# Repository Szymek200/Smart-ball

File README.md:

# ⚽ SmartBall: IoT Sports Training System

SmartBall is a comprehensive hardware and software solution designed to enhance sports training by monitoring ball dynamics in real-time. The system focuses on tracking impact force and spin (angular velocity), providing athletes with immediate feedback on their performance.

This project was developed as part of the "Microprocessor and Embedded Systems" course at the Silesian University of Technology (Politechnika Śląska).

## 📂 Repository Structure

This repository is organized into three specialized modules. For detailed technical instructions and implementation logic, please refer to the documentation within each folder:

* **/mobile-app** – Android application (Kotlin) for real-time UDP data visualization, session history, and remote sensor configuration.
* **/firmware-esp32** – ESP-IDF C code featuring high-G impact detection, quaternion-based sensor fusion (complementary filter), and power management.
* **/hardware-3d** – 3D enclosure designs (PET-G), PCB schematics, and the Bill of Materials (BOM).

## ⚙️ System Architecture

The system utilizes a **Producer-Consumer** architecture to ensure high performance and low latency:

* **The Producer (ESP32):** Equipped with an **H3LIS331DL** (400g accelerometer) and an **L3G4200D** (2000 dps gyroscope). It processes raw motion data, compensates for gravity using quaternions, and detects strikes using a circular buffer to capture pre-impact telemetry.
* **The Consumer (Mobile App):** Connects to the ball via a Wi-Fi Access Point and receives processed statistics and live streams using a high-speed binary UDP protocol.

## 🚀 Quick Start Guide

1.  **Power On:** Ensure the Li-Pol battery is charged and the device is powered.
2.  **Connect Wi-Fi:** On your mobile device, connect to the SmartBall network:
    * **SSID:** `SmartBall_ESP32`
    * **Password:** `12345678`
3.  **Launch Application:** Open the SmartBall app to begin receiving data.
4.  **Analyze:** Use the "History" section to view detailed charts of every kick, including G-force and rotation speed.

## 🔋 Power Management

To maximize the 18-hour battery life, the system includes an automated Power Management Algorithm:
* **Deep Sleep:** The MCU enters deep sleep after a configurable period of inactivity.
* **Motion Wake-up:** The accelerometer remains active as a low-power motion detector, waking the ESP32 via a hardware interrupt (GPIO 32) when the ball is moved.

## 🛠 Tech Stack Summary

* **Microcontroller:** ESP32-WROOM-32 (Dual-core).
* **Firmware:** ESP-IDF (C), FreeRTOS, LwIP (UDP).
* **Mobile App:** Kotlin, Coroutines, MPAndroidChart.
* **Mechanical:** 3D Printed PET-G, Li-Pol 1580mAh, MP2636 Power Manager.

---
*Developed by Szymon Mamok | Silesian University of Technology 2025/2026*

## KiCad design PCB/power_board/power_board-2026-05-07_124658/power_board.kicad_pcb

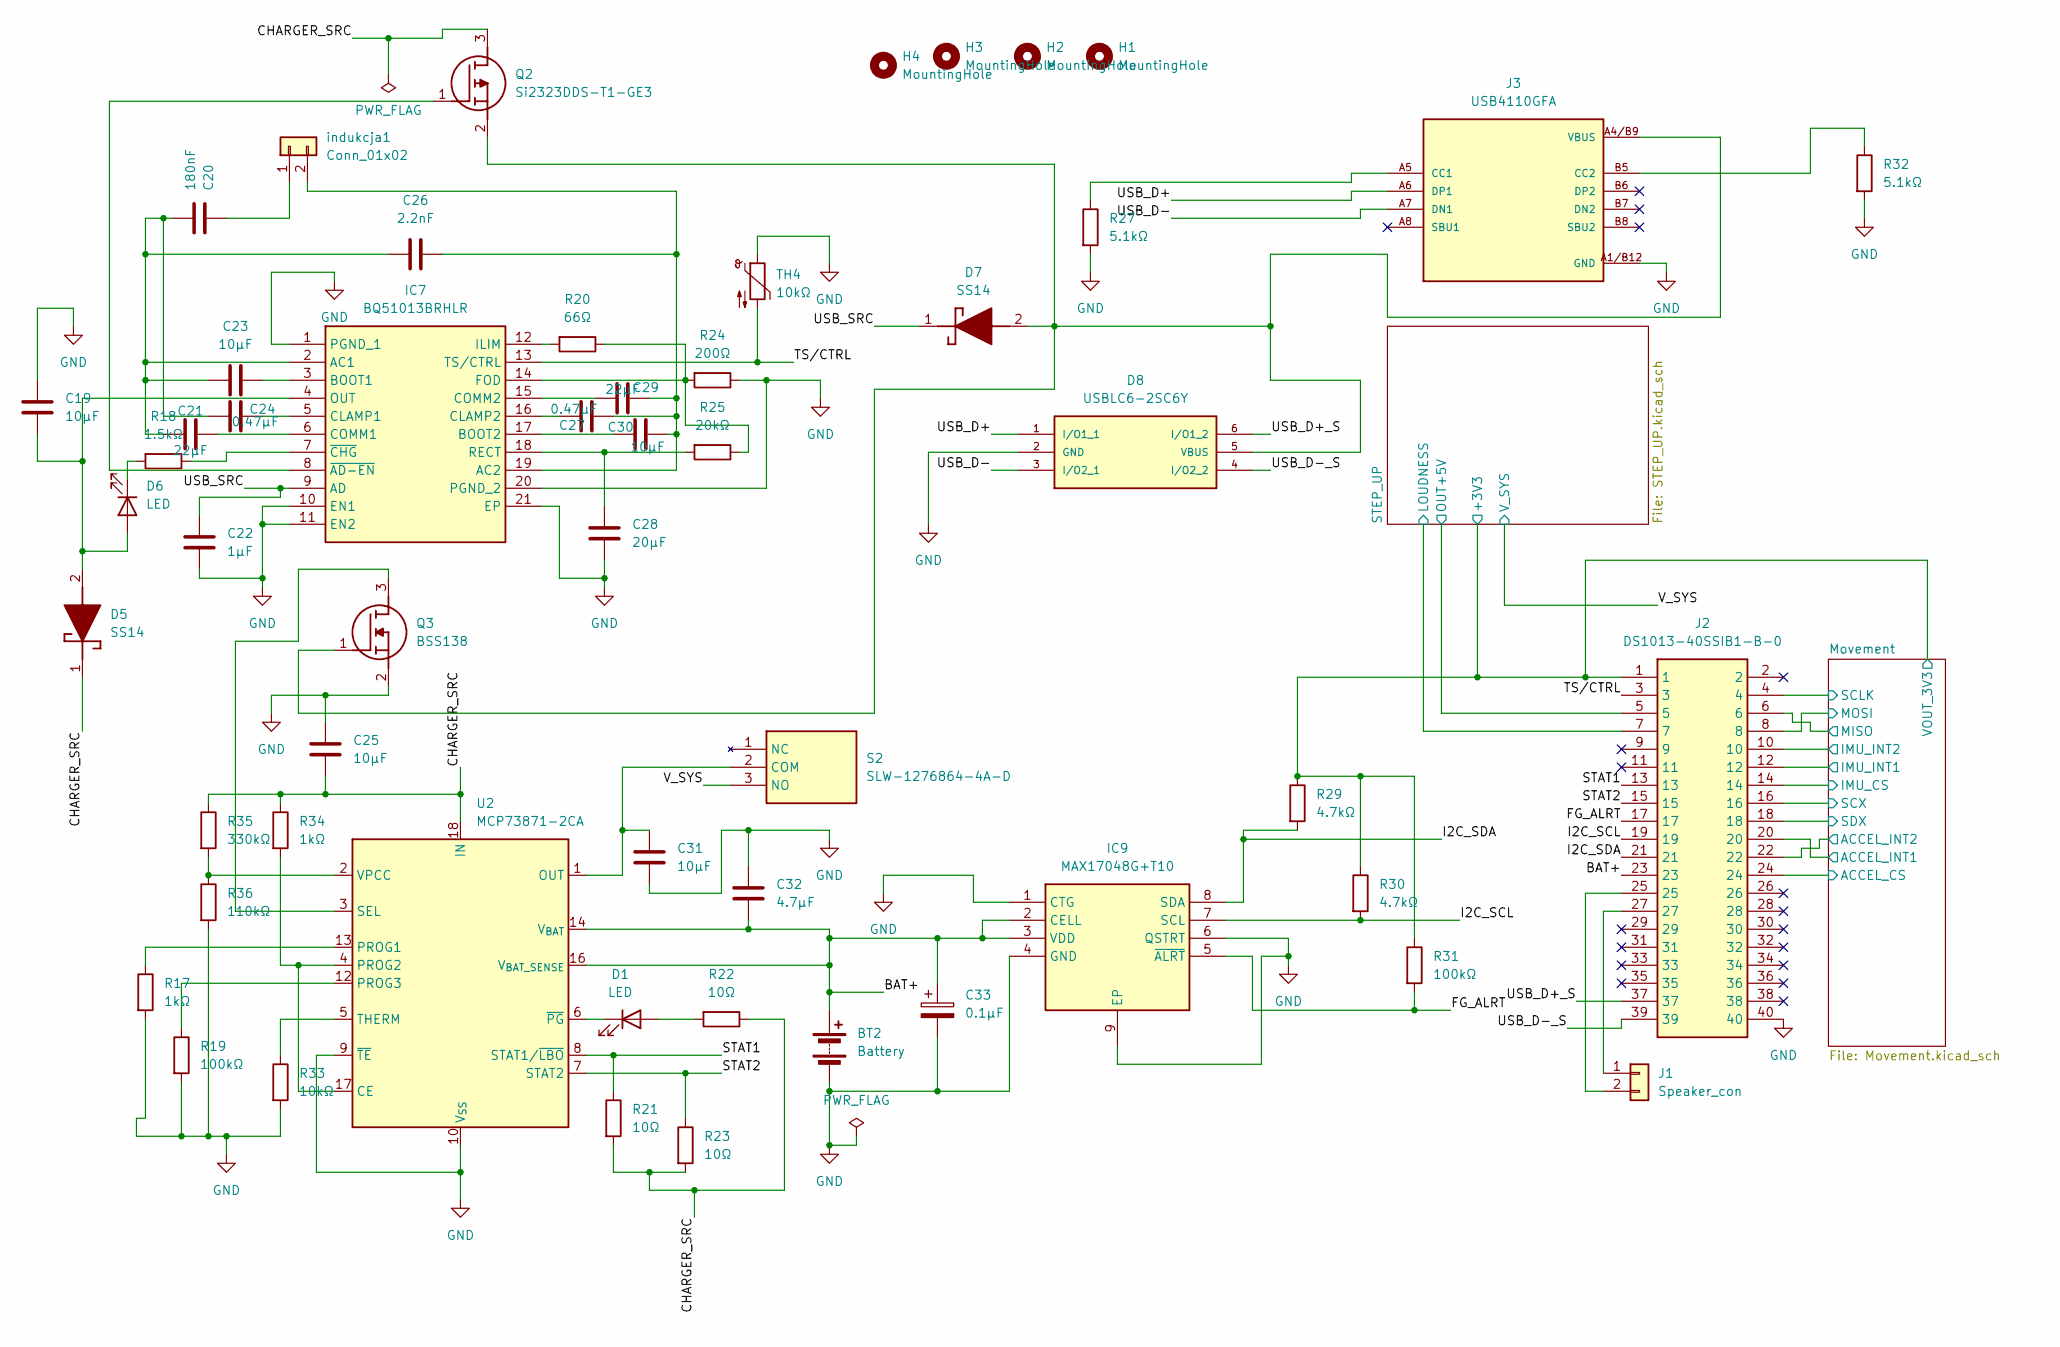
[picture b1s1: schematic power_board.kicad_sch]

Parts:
BT2: Battery; SolderWire-0.75sqmm_1x02_P4.8mm_D1.25mm_OD2.3mm
C19, C23, C25, C30, C31: 10µF; CP_EIA-3216-18_Kemet-A
C20: 180nF; CP_EIA-3216-18_Kemet-A
C21, C29: 22µF; CP_EIA-3216-18_Kemet-A
C22: 1µF; CP_EIA-3216-18_Kemet-A
C24, C27: 0.47µF; CP_EIA-3216-18_Kemet-A
C26: 2.2nF; CP_EIA-3216-18_Kemet-A
C28: 20µF; CP_EIA-3216-18_Kemet-A
C32: 4.7µF; CP_EIA-3216-18_Kemet-A
C33: 0.1µF; CP_EIA-3216-18_Kemet-A
D1, D6: LED; LED_0603_1608Metric
D5, D7: SS14; DIOM5227X270N; Mouser Part Number 512-SS14
D8: USBLC6-2SC6Y; SOT95P280X145-6N; MOUSER_PART_NUMBER 511-USBLC6-2SC6Y
H1, H2, H3, H4: MountingHole; MountingHole_3.2mm_M3_Pad_Via
IC7: BQ51013BRHLR; BQ51050BRHLR; Mouser Part Number 595-BQ51013BRHLR
IC9: MAX17048G+T10; SON50P200X200X80-9N-D; Mouser Part Number 700-MAX17048G+T10
J1: Speaker_con; PinHeader_1x02_P2.54mm_Vertical
J2: DS1013-40SSIB1-B-0; DS101340SSIB1B0; Manufacturer_Part_Number DS1013-40SSIB1-B-0
J3: USB4110GFA; GCT_USB4110GFA
Q2: Si2323DDS-T1-GE3; SOT95P237X112-3N; Mouser Part Number 78-SI2323DDS-T1-GE3
Q3: BSS138; SOT95P240X120-3N; Mouser Part Number 512-BSS138
R17, R34: 1kΩ; R_0603_1608Metric
R18: 1.5kΩ; R_0603_1608Metric
R19, R31: 100kΩ; R_0603_1608Metric
R20: 66Ω; R_0603_1608Metric
R21, R22, R23: 10Ω; R_0603_1608Metric
R24: 200Ω; R_0603_1608Metric
R25: 20kΩ; R_0603_1608Metric
R27, R32: 5.1kΩ; R_0603_1608Metric
R29, R30: 4.7kΩ; R_0603_1608Metric
R33: 10kΩ; R_0603_1608Metric
R35: 330kΩ; R_0603_1608Metric
R36: 110kΩ; R_0603_1608Metric
S2: SLW-1276864-4A-D; SLW12768644AD; Mouser Part Number 179-SLW-1276864-4A-D
TH4: 10kΩ; R_0603_1608Metric
U2: MCP73871-2CA; QFN-20-1EP_4x4mm_P0.5mm_EP2.5x2.5mm
indukcja1: Conn_01x02; PinHeader_1x02_P2.54mm_Vertical

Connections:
/BAT+: BT2.1 (+), C32.2, C33.1, IC9.2 (CELL), IC9.3 (VDD), J2.23, U2.14 (V_{BAT}), U2.15 (V_{BAT}), U2.16 (V_{BAT_SENSE})
/CHARGER_SRC: C25.2, D5.1 (K), Q2.3 (D), R21.2, R22.1, R23.2, R34.1, R35.1, U2.18 (IN), U2.19 (IN)
/FG_ALRT: IC9.5 (~ALRT), J2.17, R31.2
/I2C_SCL: IC9.7 (SCL), J2.19, R30.2
/I2C_SDA: IC9.8 (SDA), J2.21, R29.2
/Movement/ACCEL_CS: J2.24; also elsewhere on the board
/Movement/ACCEL_INT1: J2.20; also elsewhere on the board
/Movement/ACCEL_INT2: J2.22; also elsewhere on the board
/Movement/IMU_CS: J2.14; also elsewhere on the board
/Movement/IMU_INT1: J2.12; also elsewhere on the board
/Movement/IMU_INT2: J2.10; also elsewhere on the board
/Movement/MISO: J2.6; also elsewhere on the board
/Movement/MOSI: J2.8; also elsewhere on the board
/Movement/SCLK: J2.4; also elsewhere on the board
/Movement/SCX: J2.16; also elsewhere on the board
/Movement/SDX: J2.18; also elsewhere on the board
/Movement/VOUT_3V3: J2.1, R29.1, R30.1, R31.1; also elsewhere on the board
/STAT1: J2.13, R21.1, U2.8 (STAT1/~LBO)
/STAT2: J2.15, R23.1, U2.7 (STAT2)
/STEP_UP/LOUDNESS: J2.7; also elsewhere on the board
/STEP_UP/OUT+5V: J2.5; also elsewhere on the board
/TS/CTRL: IC7.13 (TS/CTRL), J2.3, TH4.2
/USB_D+: D8.1 (I/O1_1), J3.A6 (DP1)
/USB_D+_S: D8.6 (I/O1_2), J2.37
/USB_D-: D8.3 (I/O2_1), J3.A7 (DN1)
/USB_D-_S: D8.4 (I/O2_2), J2.39
/USB_SRC: C22.1, D7.1 (K), IC7.9 (AD)
/V_SYS: S2.3 (NO); also elsewhere on the board
GND: BT2.2 (-), C19.2, C22.2, C25.1, C28.2, C31.2, C32.1, C33.2, D8.2 (GND), IC7.1 (PGND_1), IC7.10 (EN1), IC7.11 (EN2), IC7.20 (PGND_2), IC7.21 (EP), IC9.1 (CTG), IC9.4 (GND), IC9.6 (QSTRT), IC9.9 (EP), J2.40, J3.A1/B12 (GND), J3.B1/A12 (GND), J3.S1 (GND), J3.S2 (GND), J3.S3 (GND), J3.S4 (GND), Q3.2 (S), R17.2, R19.2, R24.1, R27.2, R32.2, R33.2, R36.2, TH4.1, U2.9 (~TE), U2.10 (V_{SS}), U2.11 (V_{SS}), U2.21 (V_{SS}); also elsewhere on the board
unnamed: D1.2 (A), R22.2
unnamed: D1.1 (K), U2.6 (~PG)
unnamed: C19.1, D5.2 (A), D6.2 (A), IC7.4 (OUT)
unnamed: D6.1 (K), R18.2
unnamed: C20.2, C21.2, C23.2, C24.2, C26.2, IC7.2 (AC1)
unnamed: C26.1, C27.1, C29.1, C30.1, IC7.19 (AC2), indukcja1.2
unnamed: C23.1, IC7.3 (BOOT1)
unnamed: C30.2, IC7.17 (BOOT2)
unnamed: C24.1, IC7.5 (CLAMP1)
unnamed: C27.2, IC7.16 (CLAMP2)
unnamed: C21.1, IC7.6 (COMM1)
unnamed: C29.2, IC7.15 (COMM2)
unnamed: IC7.14 (FOD), R20.1, R24.2, R25.1
unnamed: IC7.12 (ILIM), R20.2
unnamed: C28.1, IC7.18 (RECT), R25.2
unnamed: IC7.8 (~AD-EN), Q2.1 (G)
unnamed: IC7.7 (~CHG), R18.1
unnamed: J1.1, J2.27
unnamed: J1.2, J2.25
unnamed: J3.A5 (CC1), R27.1
unnamed: J3.B5 (CC2), R32.1
unnamed: Q3.3 (D), U2.3 (SEL)
unnamed: C31.1, S2.2 (COM), U2.1 (OUT), U2.20 (OUT)
unnamed: R34.2, U2.4 (PROG2), U2.17 (CE)
unnamed: R17.1, U2.13 (PROG1)
unnamed: R19.1, U2.12 (PROG3)
unnamed: R33.1, U2.5 (THERM)
unnamed: R35.2, R36.1, U2.2 (VPCC)
unnamed: C20.1, indukcja1.1
VBUS: D7.2 (A), D8.5 (VBUS), J3.A4/B9 (VBUS), J3.B4/A9 (VBUS), Q2.2 (S), Q3.1 (G)

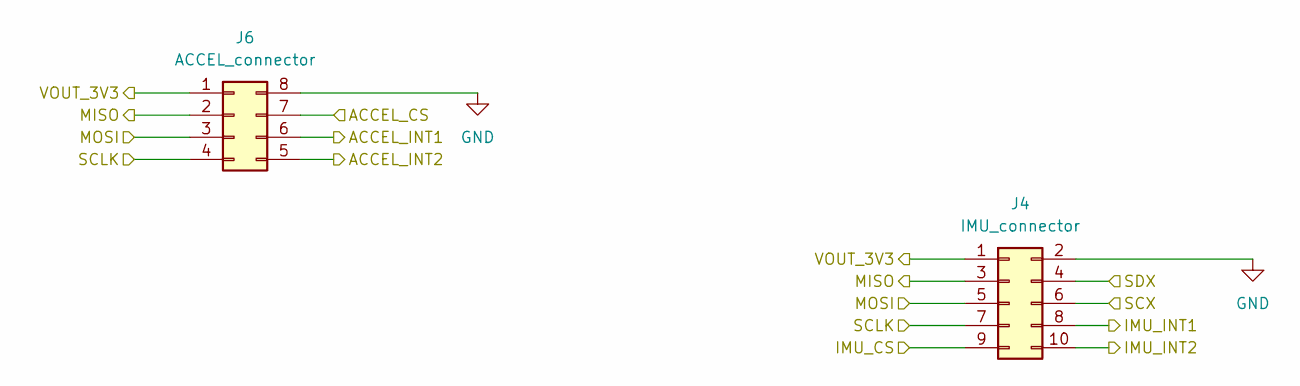
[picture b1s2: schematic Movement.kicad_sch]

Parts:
J4: IMU_connector; PinHeader_2x05_P2.54mm_Vertical
J6: ACCEL_connector; PinHeader_2x04_P2.54mm_Vertical

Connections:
/Movement/ACCEL_CS: J6.7; also elsewhere on the board
/Movement/ACCEL_INT1: J6.6; also elsewhere on the board
/Movement/ACCEL_INT2: J6.5; also elsewhere on the board
/Movement/IMU_CS: J4.9; also elsewhere on the board
/Movement/IMU_INT1: J4.8; also elsewhere on the board
/Movement/IMU_INT2: J4.10; also elsewhere on the board
/Movement/MISO: J4.3, J6.2; also elsewhere on the board
/Movement/MOSI: J4.5, J6.3; also elsewhere on the board
/Movement/SCLK: J4.7, J6.4; also elsewhere on the board
/Movement/SCX: J4.6; also elsewhere on the board
/Movement/SDX: J4.4; also elsewhere on the board
/Movement/VOUT_3V3: J4.1, J6.1; also elsewhere on the board
GND: J4.2, J6.8; also elsewhere on the board

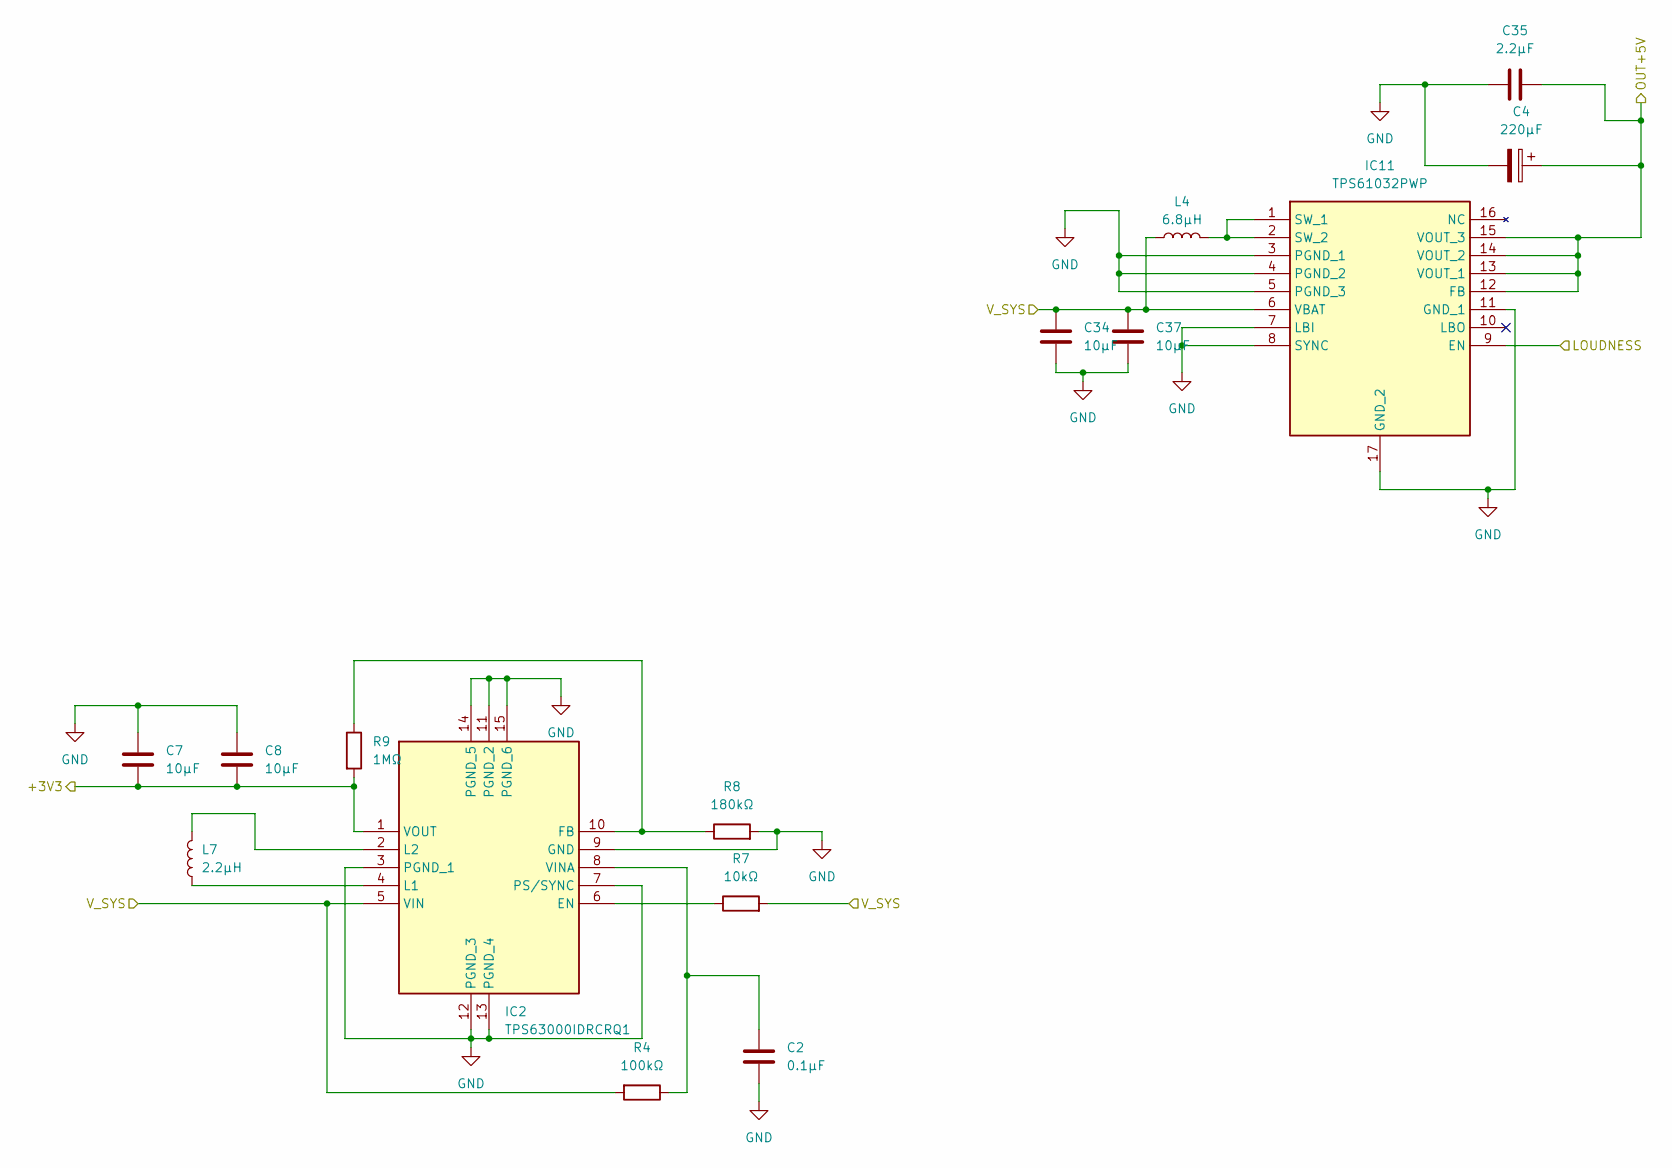
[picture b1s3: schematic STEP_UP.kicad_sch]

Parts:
C2: 0.1μF; CP_Elec_6.3x5.4
C4: 220µF; CP_Elec_6.3x5.4
C7, C8: 10μF; CP_Elec_6.3x5.4
C34, C37: 10µF; CP_Elec_6.3x5.4
C35: 2.2µF; CP_Elec_6.3x5.4
IC2: TPS63000IDRCRQ1; Mouser Part Number 595-TPS63000IDRCRQ1
IC11: TPS61032PWP; SOP65P640X120-17N; Mouser Part Number 595-TPS61032PWP
L4: 6.8µH; L_6.3x6.3_H3
L7: 2.2µH; L_6.3x6.3_H3
R4: 100kΩ; R_0603_1608Metric
R7: 10kΩ; R_0603_1608Metric
R8: 180kΩ; R_0603_1608Metric
R9: 1MΩ; R_0603_1608Metric

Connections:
/Movement/VOUT_3V3: C7.2, C8.2, IC2.1 (VOUT), R9.2; also elsewhere on the board
/STEP_UP/LOUDNESS: IC11.9 (EN); also elsewhere on the board
/STEP_UP/OUT+5V: C4.1, C35.2, IC11.12 (FB), IC11.13 (VOUT_1), IC11.14 (VOUT_2), IC11.15 (VOUT_3); also elsewhere on the board
/V_SYS: C34.1, C37.1, IC2.5 (VIN), IC11.6 (VBAT), L4.1, R4.2, R7.2; also elsewhere on the board
GND: C2.2, C4.2, C7.1, C8.1, C34.2, C35.1, C37.2, IC2.3 (PGND_1), IC2.7 (PS/SYNC), IC2.9 (GND), IC2.11 (PGND_2), IC2.12 (PGND_3), IC2.13 (PGND_4), IC2.14 (PGND_5), IC2.15 (PGND_6), IC11.3 (PGND_1), IC11.4 (PGND_2), IC11.5 (PGND_3), IC11.7 (LBI), IC11.8 (SYNC), IC11.11 (GND_1), IC11.17 (GND_2), R8.2; also elsewhere on the board
unnamed: IC2.6 (EN), R7.1
unnamed: IC2.10 (FB), R8.1, R9.1
unnamed: IC2.4 (L1), L7.1
unnamed: IC2.2 (L2), L7.2
unnamed: C2.1, IC2.8 (VINA), R4.1
unnamed: IC11.1 (SW_1), IC11.2 (SW_2), L4.2

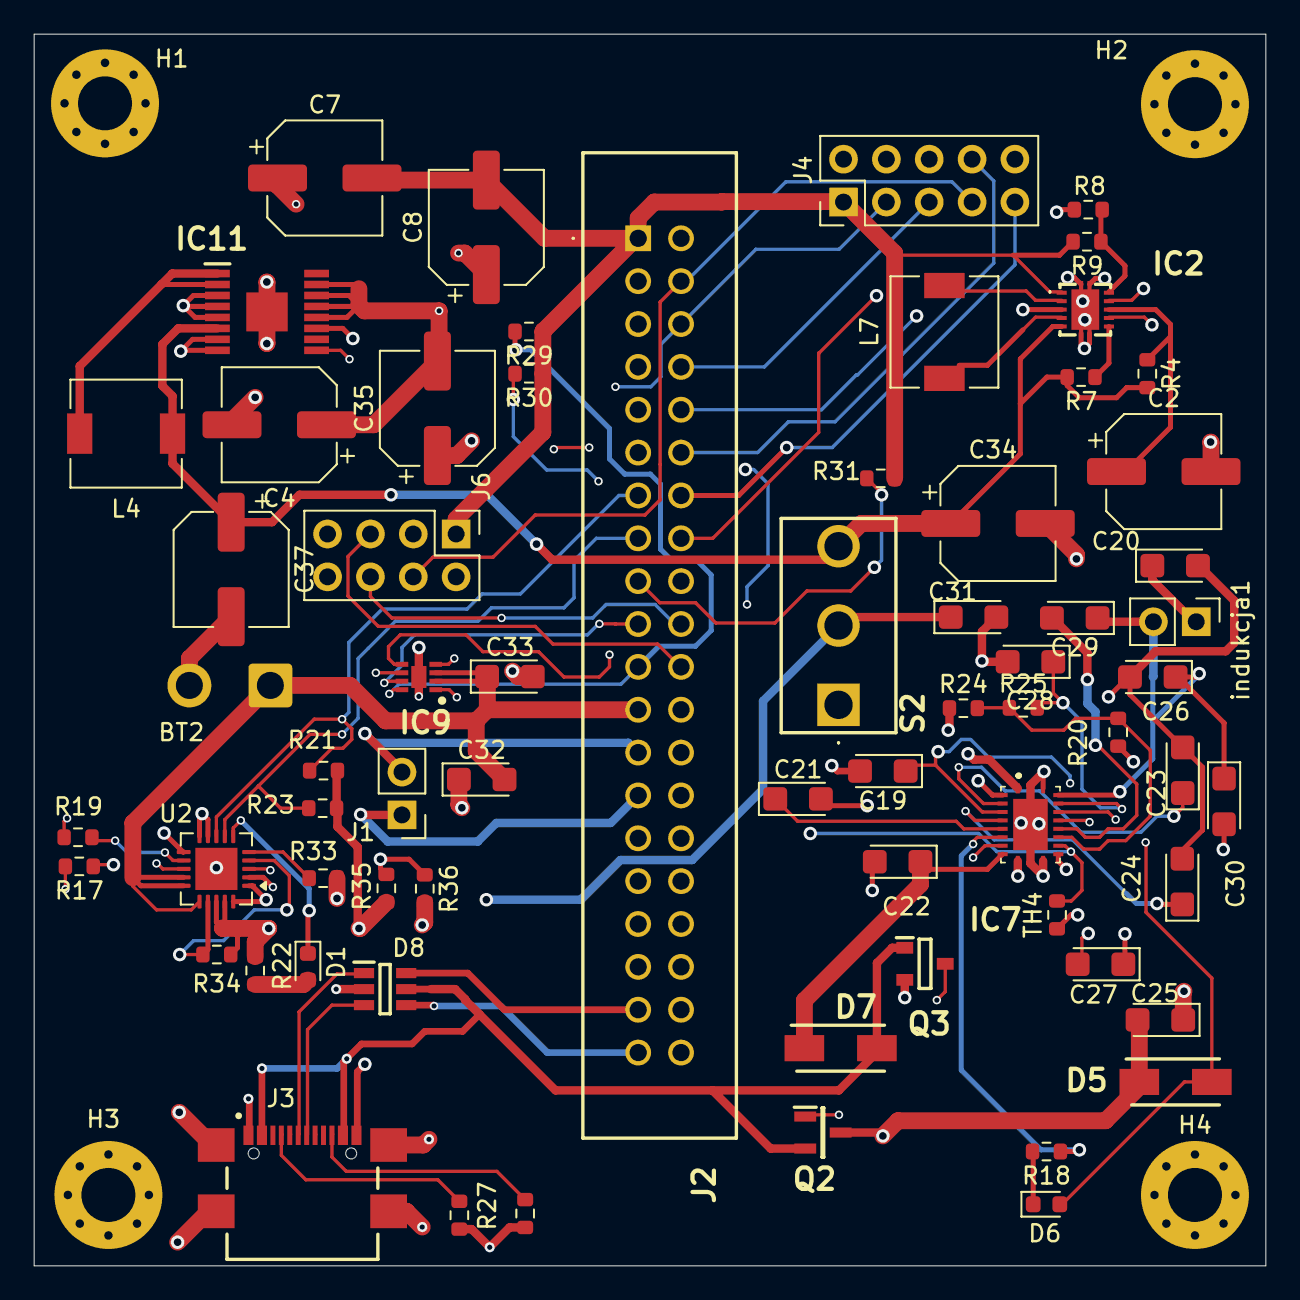
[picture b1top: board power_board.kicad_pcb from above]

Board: 4 copper layers, 73.0 x 73.0 mm, 71 parts (0 on the bottom side), 65 nets.

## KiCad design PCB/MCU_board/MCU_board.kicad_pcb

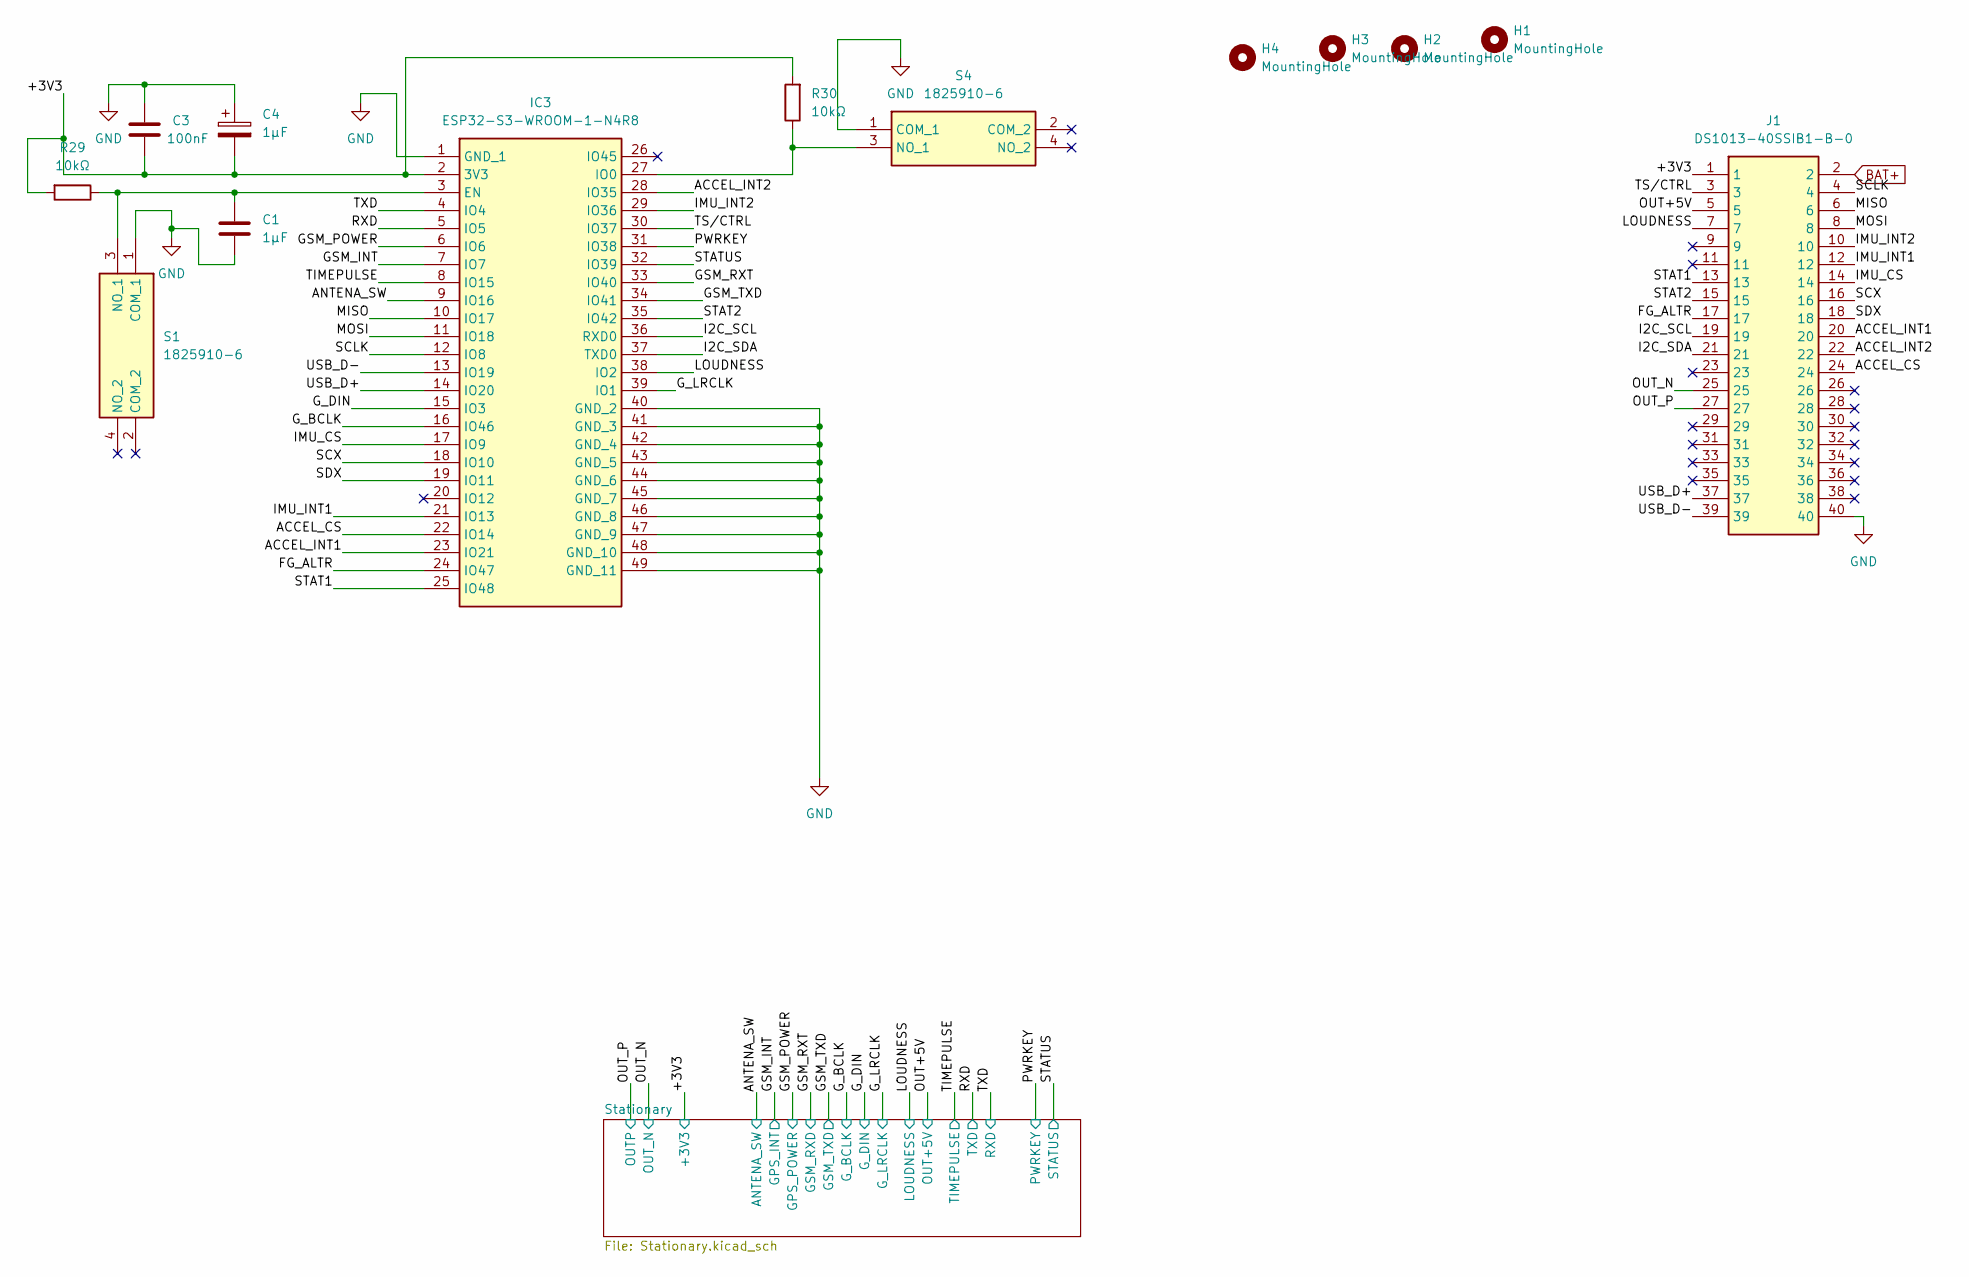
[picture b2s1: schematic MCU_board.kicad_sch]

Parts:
C1: 1μF; CP_Elec_6.3x5.4
C3: 100nF; CP_Elec_6.3x5.4
C4: 1μF; CP_EIA-3216-18_Kemet-A
H1, H2, H3, H4: MountingHole; MountingHole_3.2mm_M3_Pad_Via
IC3: ESP32-S3-WROOM-1-N4R8; ESP32S3WROOM1N4R8; Mouser Part Number 356-ESP32S3WROM1N4R8
J1: DS1013-40SSIB1-B-0; DS101340SSIB1B0; Manufacturer_Part_Number DS1013-40SSIB1-B-0
R29, R30: 10kΩ; R_0603_1608Metric
S1, S4: 1825910-6; 18259106; Manufacturer_Part_Number 1825910-6

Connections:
/+3V3: C3.2, C4.2, IC3.2 (3V3), J1.1, R29.2, R30.2; also elsewhere on the board
/ACCEL_CS: IC3.22 (IO14), J1.24
/ACCEL_INT1: IC3.23 (IO21), J1.20
/ACCEL_INT2: IC3.28 (IO35), J1.22
/ANTENA_SW: IC3.9 (IO16); also elsewhere on the board
/FG_ALTR: IC3.24 (IO47), J1.17
/GSM_INT: IC3.7 (IO7); also elsewhere on the board
/GSM_POWER: IC3.6 (IO6); also elsewhere on the board
/GSM_RXT: IC3.33 (IO40); also elsewhere on the board
/GSM_TXD: IC3.34 (IO41); also elsewhere on the board
/G_BCLK: IC3.16 (IO46); also elsewhere on the board
/G_DIN: IC3.15 (IO3); also elsewhere on the board
/G_LRCLK: IC3.39 (IO1); also elsewhere on the board
/I2C_SCL: IC3.36 (RXD0), J1.19
/I2C_SDA: IC3.37 (TXD0), J1.21
/IMU_CS: IC3.17 (IO9), J1.14
/IMU_INT1: IC3.21 (IO13), J1.12
/IMU_INT2: IC3.29 (IO36), J1.10
/LOUDNESS: IC3.38 (IO2), J1.7; also elsewhere on the board
/MISO: IC3.10 (IO17), J1.6
/MOSI: IC3.11 (IO18), J1.8
/OUT+5V: J1.5; also elsewhere on the board
/OUT_N: J1.25; also elsewhere on the board
/OUT_P: J1.27; also elsewhere on the board
/PWRKEY: IC3.31 (IO38); also elsewhere on the board
/RXD: IC3.5 (IO5); also elsewhere on the board
/SCLK: IC3.12 (IO8), J1.4
/SCX: IC3.18 (IO10), J1.16
/SDX: IC3.19 (IO11), J1.18
/STAT1: IC3.25 (IO48), J1.13
/STAT2: IC3.35 (IO42), J1.15
/STATUS: IC3.32 (IO39); also elsewhere on the board
/TIMEPULSE: IC3.8 (IO15); also elsewhere on the board
/TS/CTRL: IC3.30 (IO37), J1.3
/TXD: IC3.4 (IO4); also elsewhere on the board
/USB_D+: IC3.14 (IO20), J1.37
/USB_D-: IC3.13 (IO19), J1.39
BAT+: J1.2; also elsewhere on the board
GND: C1.2, C3.1, C4.1, IC3.1 (GND_1), IC3.40 (GND_2), IC3.41 (GND_3), IC3.42 (GND_4), IC3.43 (GND_5), IC3.44 (GND_6), IC3.45 (GND_7), IC3.46 (GND_8), IC3.47 (GND_9), IC3.48 (GND_10), IC3.49 (GND_11), J1.40, S1.1 (COM_1), S4.1 (COM_1); also elsewhere on the board
unnamed: C1.1, IC3.3 (EN), R29.1, S1.3 (NO_1)
unnamed: IC3.27 (IO0), R30.1, S4.3 (NO_1)

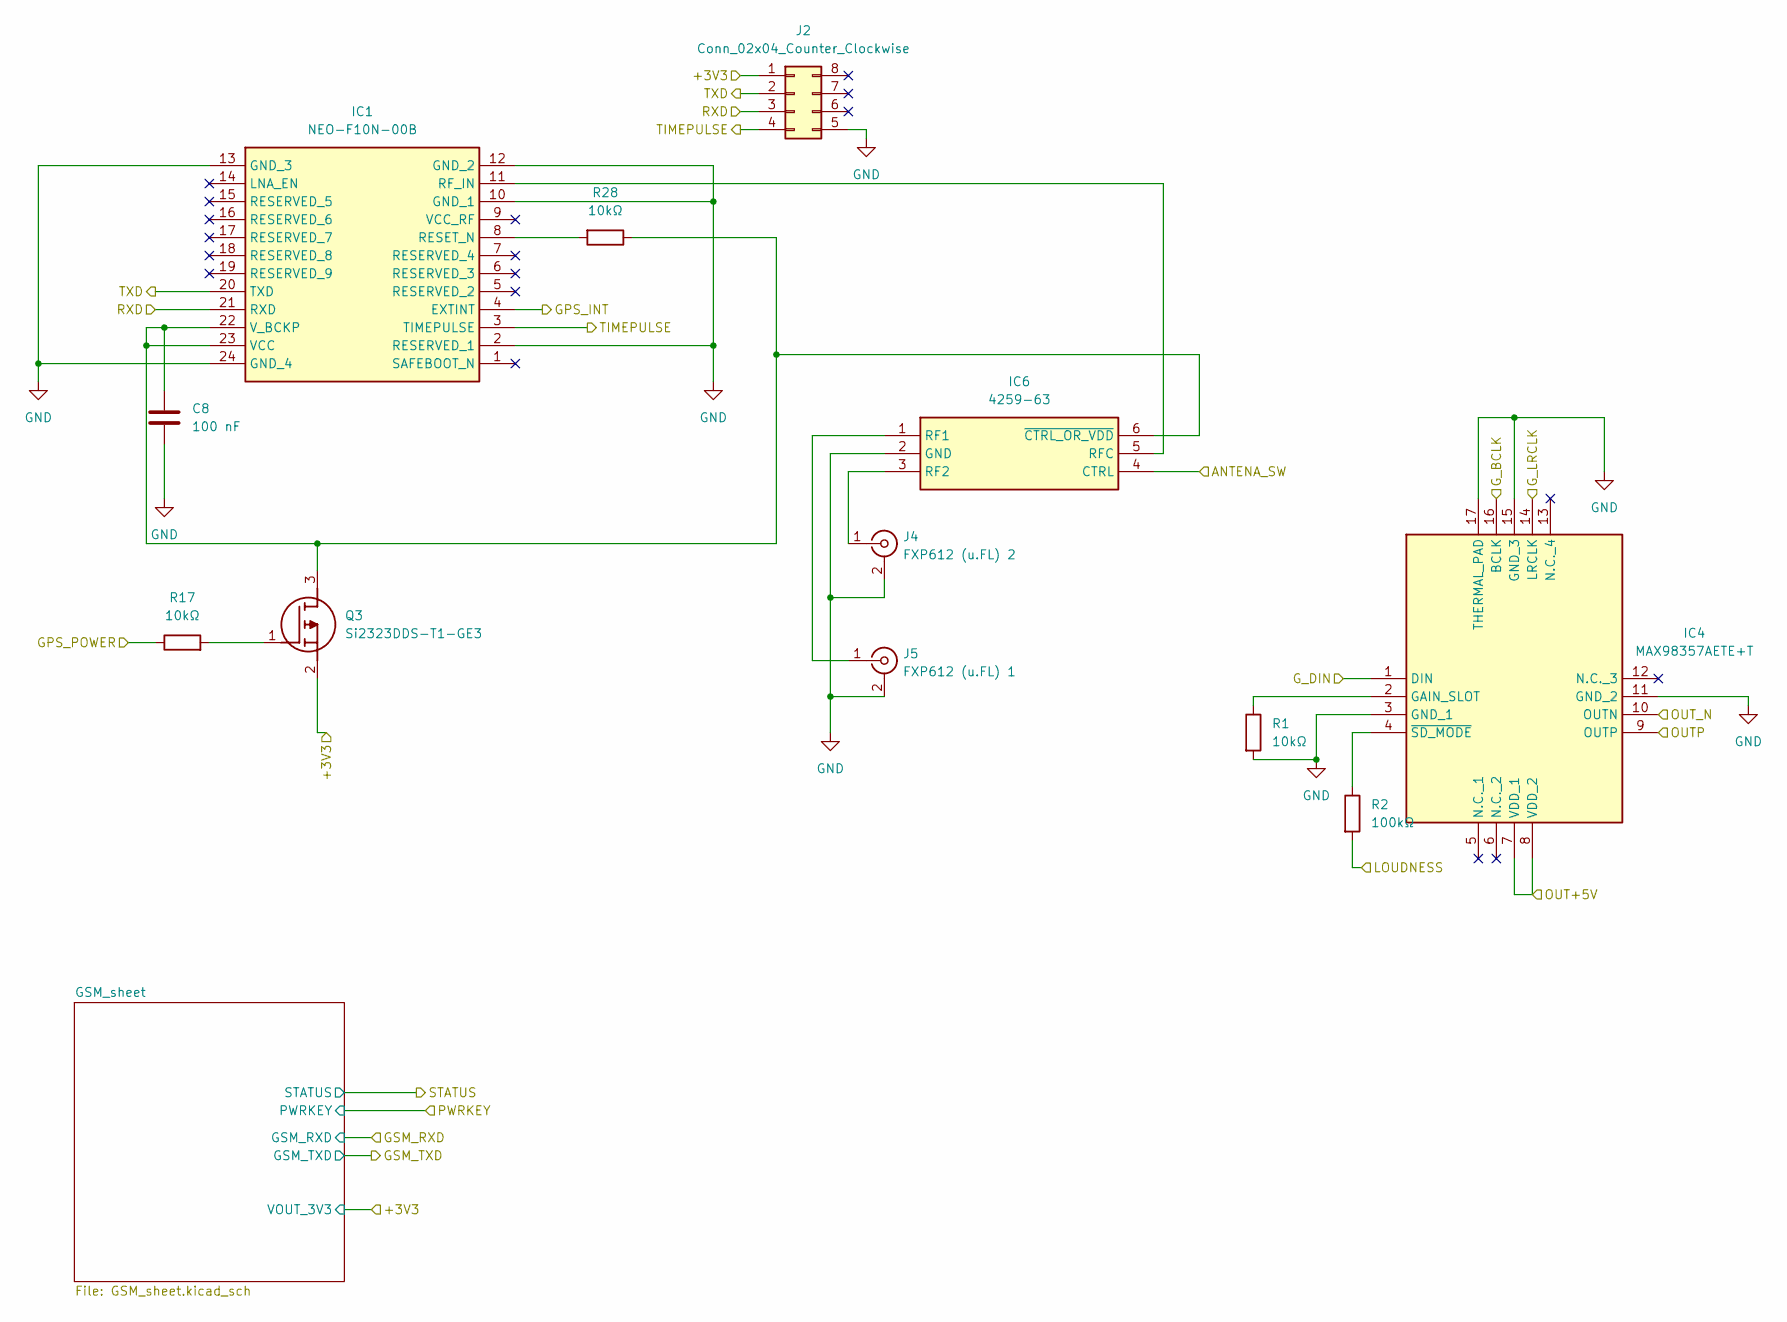
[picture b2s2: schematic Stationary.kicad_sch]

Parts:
C8: 100 nF; CP_Elec_6.3x5.4
IC1: NEO-F10N-00B; NEOF10N00B; Mouser Part Number 377-NEO-F10N-00B
IC4: MAX98357AETE+T; QFN50P300X300X80-17N; Mouser Part Number 700-MAX98357AETE+T
IC6: 4259-63; SOT65P210X110-6N; Mouser Part Number 81-4259-63
J2: Conn_02x04_Counter_Clockwise; PinHeader_2x04_P2.54mm_Vertical
J4: FXP612 (u.FL) 2; U.FL_Molex_MCRF_73412-0110_Vertical
J5: FXP612 (u.FL) 1; U.FL_Molex_MCRF_73412-0110_Vertical
Q3: Si2323DDS-T1-GE3; SOT-23; Mouser Part Number 78-SI2323DDS-T1-GE3
R1, R17, R28: 10kΩ; R_0603_1608Metric
R2: 100kΩ; R_0603_1608Metric

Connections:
/+3V3: J2.1, Q3.2 (S); also elsewhere on the board
/ANTENA_SW: IC6.4 (CTRL); also elsewhere on the board
/GSM_INT: IC1.4 (EXTINT); also elsewhere on the board
/GSM_POWER: R17.1; also elsewhere on the board
/G_BCLK: IC4.16 (BCLK); also elsewhere on the board
/G_DIN: IC4.1 (DIN); also elsewhere on the board
/G_LRCLK: IC4.14 (LRCLK); also elsewhere on the board
/LOUDNESS: R2.2; also elsewhere on the board
/OUT+5V: IC4.7 (VDD_1), IC4.8 (VDD_2); also elsewhere on the board
/OUT_N: IC4.10 (OUTN); also elsewhere on the board
/OUT_P: IC4.9 (OUTP); also elsewhere on the board
/RXD: IC1.20 (TXD), J2.2; also elsewhere on the board
/TIMEPULSE: IC1.3 (TIMEPULSE), J2.4; also elsewhere on the board
/TXD: IC1.21 (RXD), J2.3; also elsewhere on the board
GND: C8.2, IC1.2 (RESERVED_1), IC1.10 (GND_1), IC1.12 (GND_2), IC1.13 (GND_3), IC1.24 (GND_4), IC4.3 (GND_1), IC4.11 (GND_2), IC4.15 (GND_3), IC4.17 (THERMAL_PAD), IC6.2 (GND), J2.5, J4.2 (Ext), J5.2 (Ext), R1.2; also elsewhere on the board
unnamed: IC1.8 (RESET_N), R28.2
unnamed: IC1.11 (RF_IN), IC6.5 (RFC)
unnamed: C8.1, IC1.22 (V_BCKP), IC1.23 (VCC), IC6.6 (~CTRL_OR_VDD), Q3.3 (D), R28.1
unnamed: IC4.2 (GAIN_SLOT), R1.1
unnamed: IC4.4 (~SD_MODE), R2.1
unnamed: IC6.1 (RF1), J5.1 (In)
unnamed: IC6.3 (RF2), J4.1 (In)
unnamed: Q3.1 (G), R17.2
